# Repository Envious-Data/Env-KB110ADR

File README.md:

# Env-KB110ADR
A STM32F411CEU6 powered Mechanical keyboard PCB designed in KiCad

- Project Name: Env-KB110ADR
- Nickname: Victus

### About
I originally helped a friend design this but he couldnt quite figure out kicad nor had the motivation, It started out as a RP2040 powered 110% layout and then got cut down to a normal 100% and switched to a STM32F411CEU6.

It also support hotswap and ansi+iso.

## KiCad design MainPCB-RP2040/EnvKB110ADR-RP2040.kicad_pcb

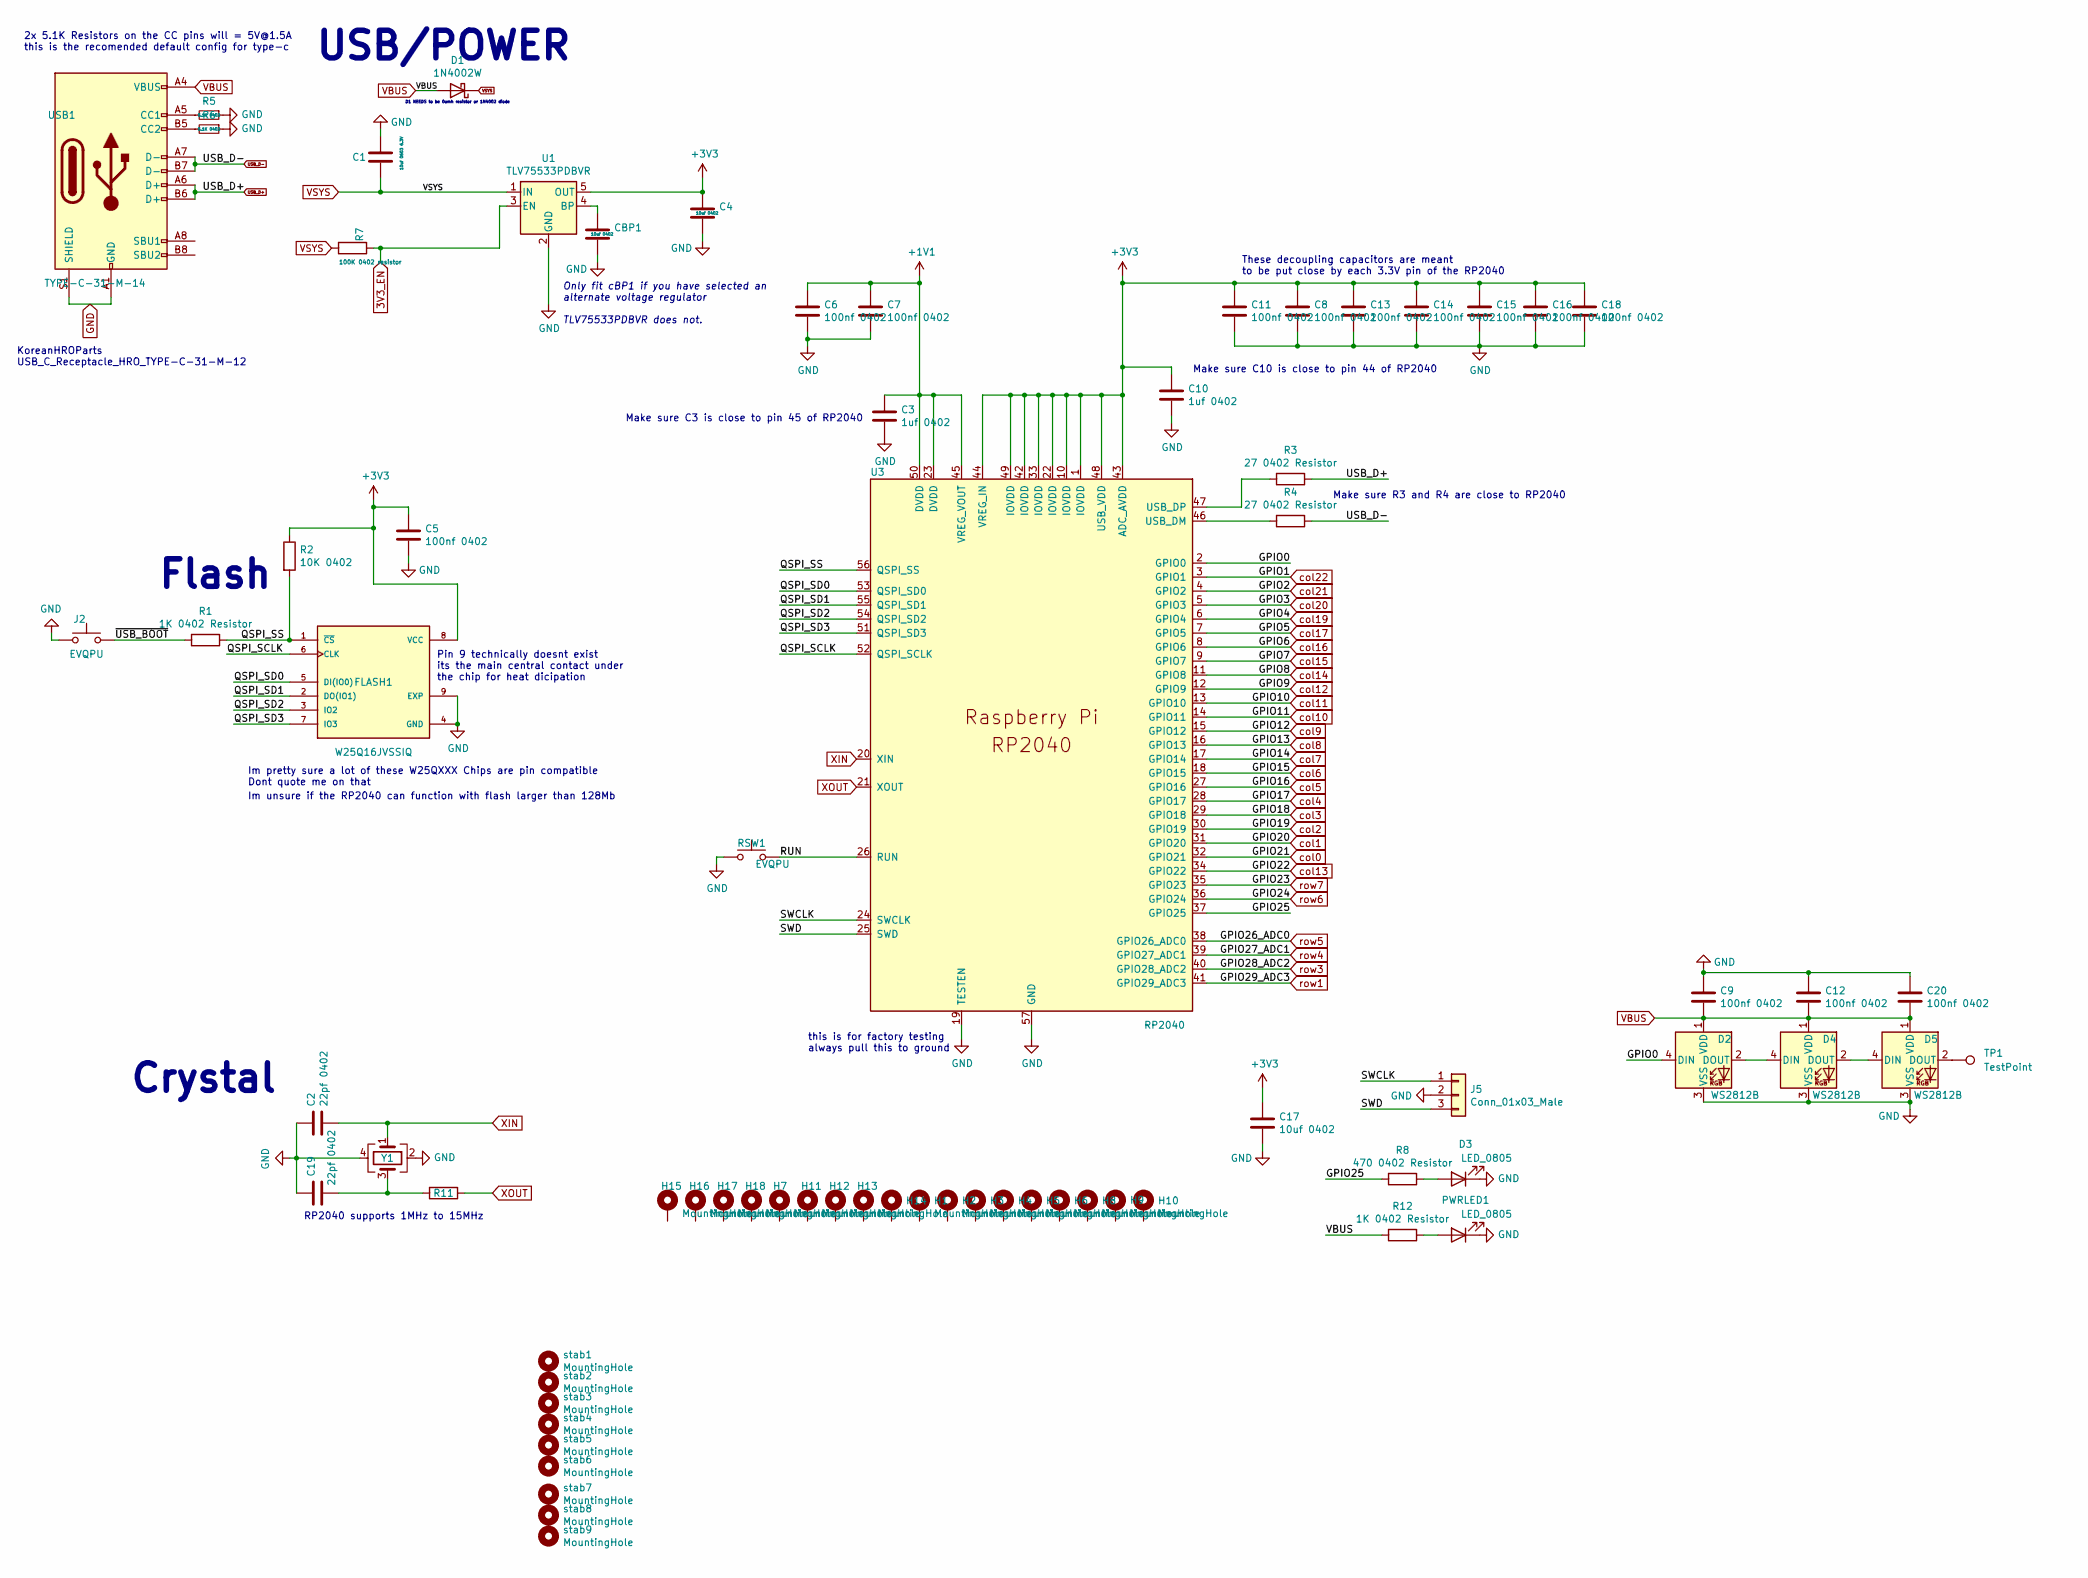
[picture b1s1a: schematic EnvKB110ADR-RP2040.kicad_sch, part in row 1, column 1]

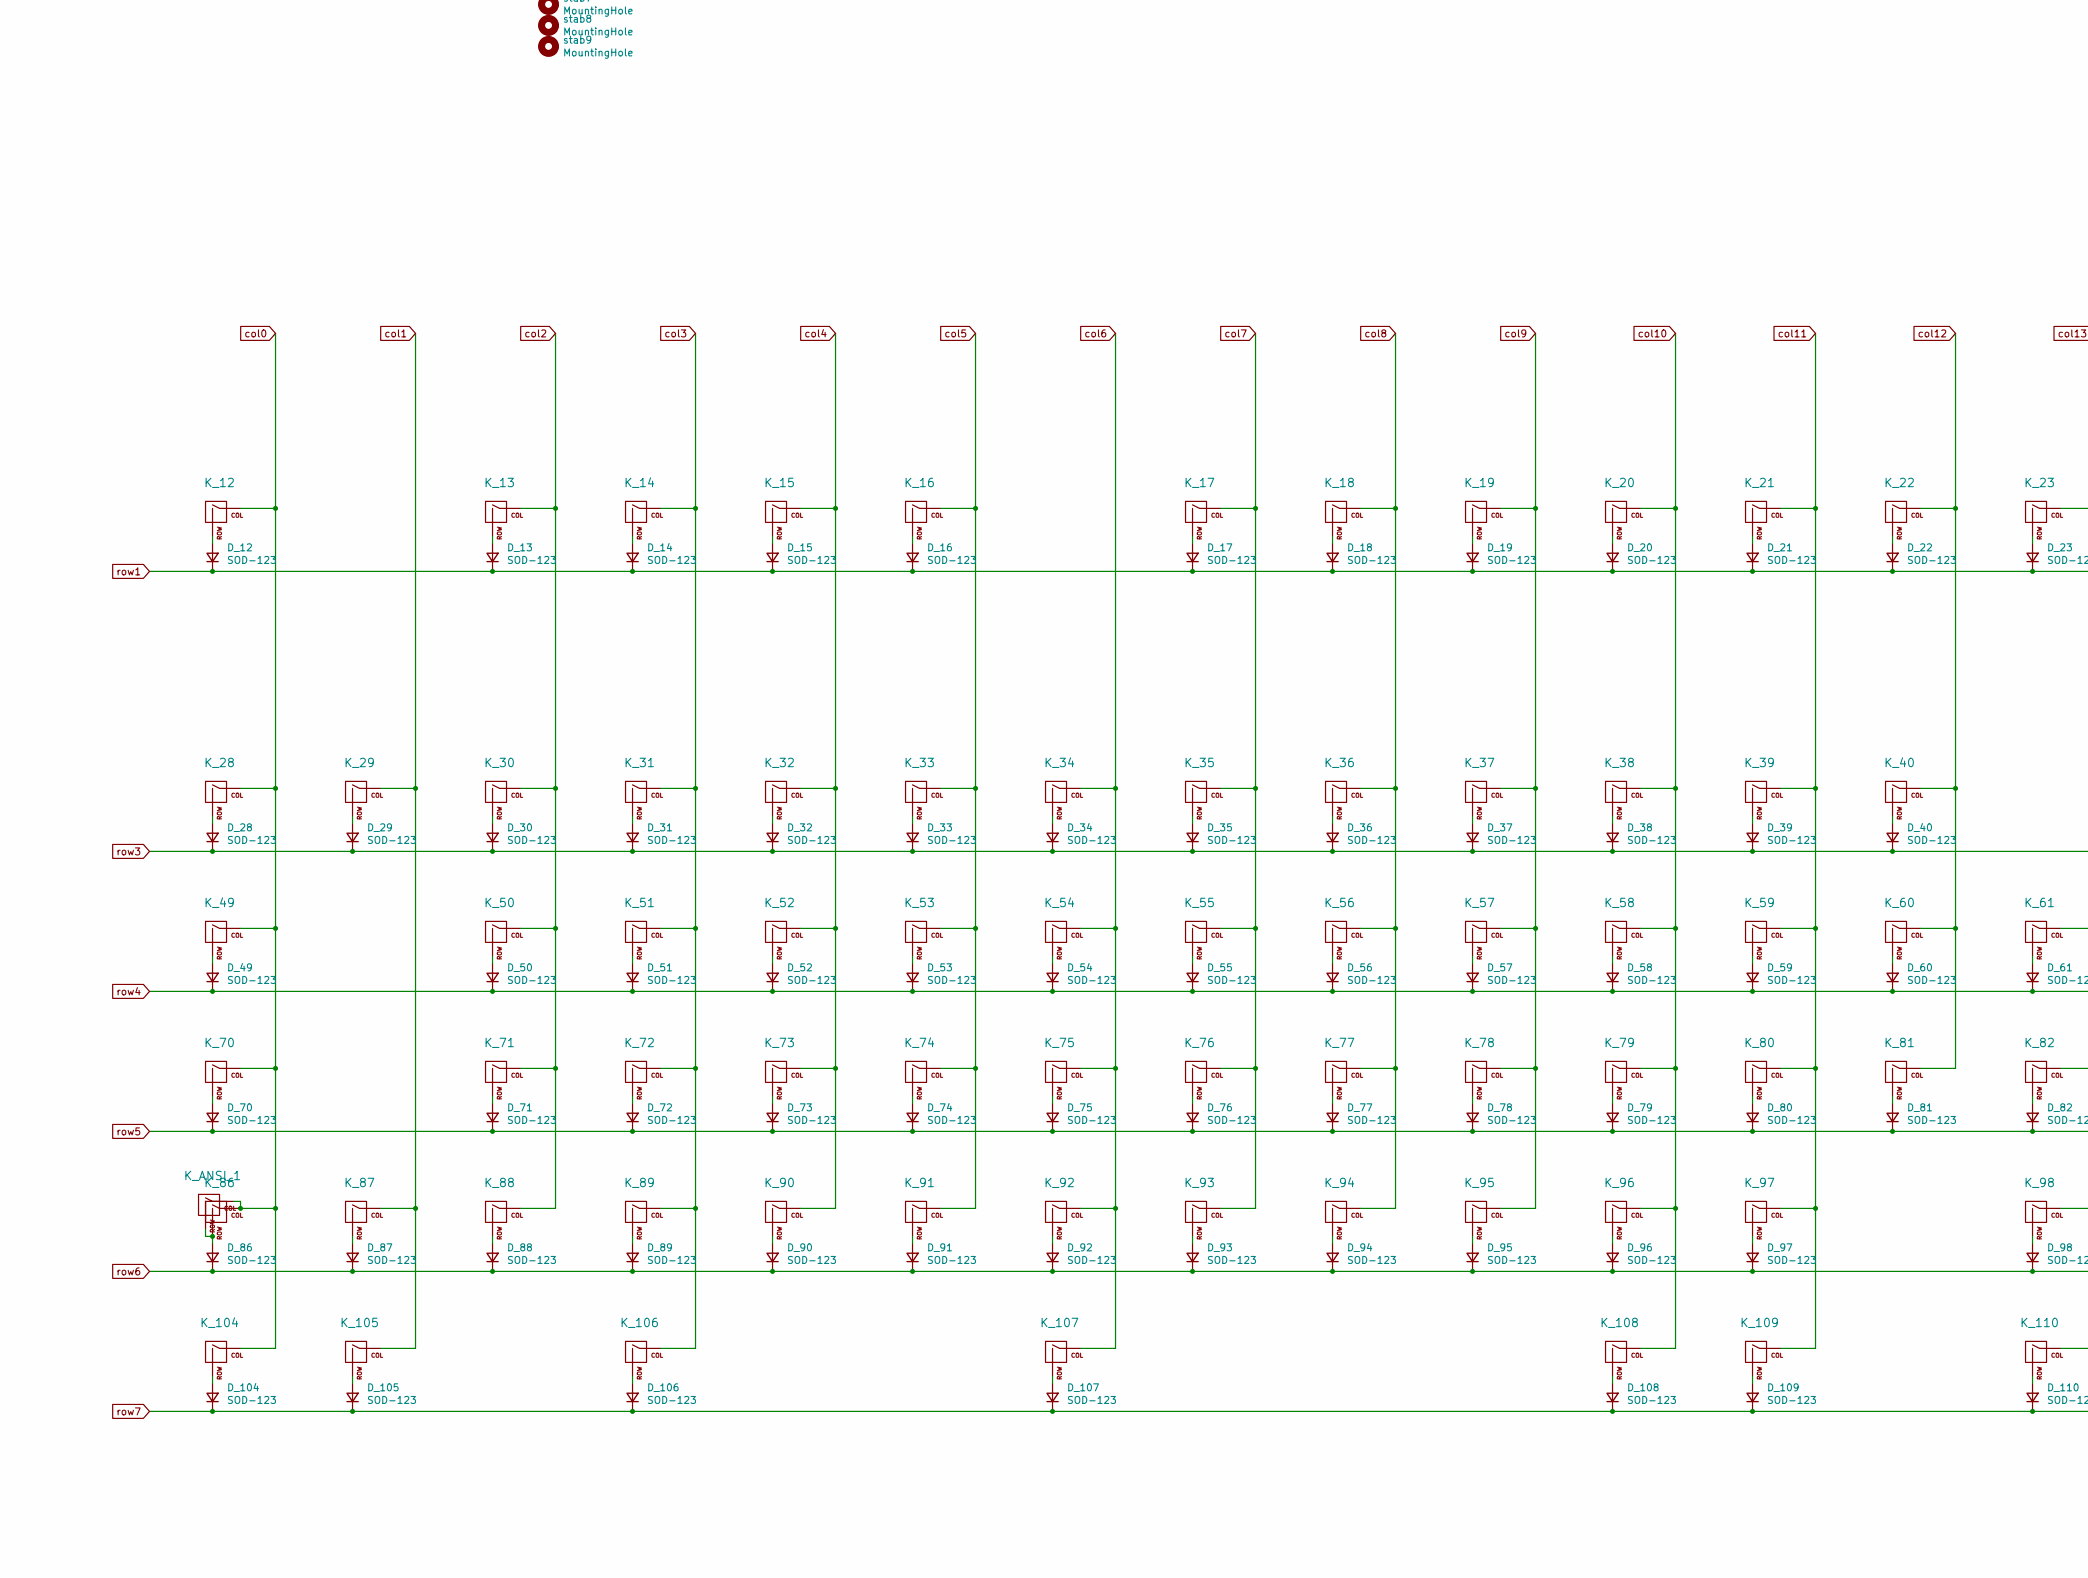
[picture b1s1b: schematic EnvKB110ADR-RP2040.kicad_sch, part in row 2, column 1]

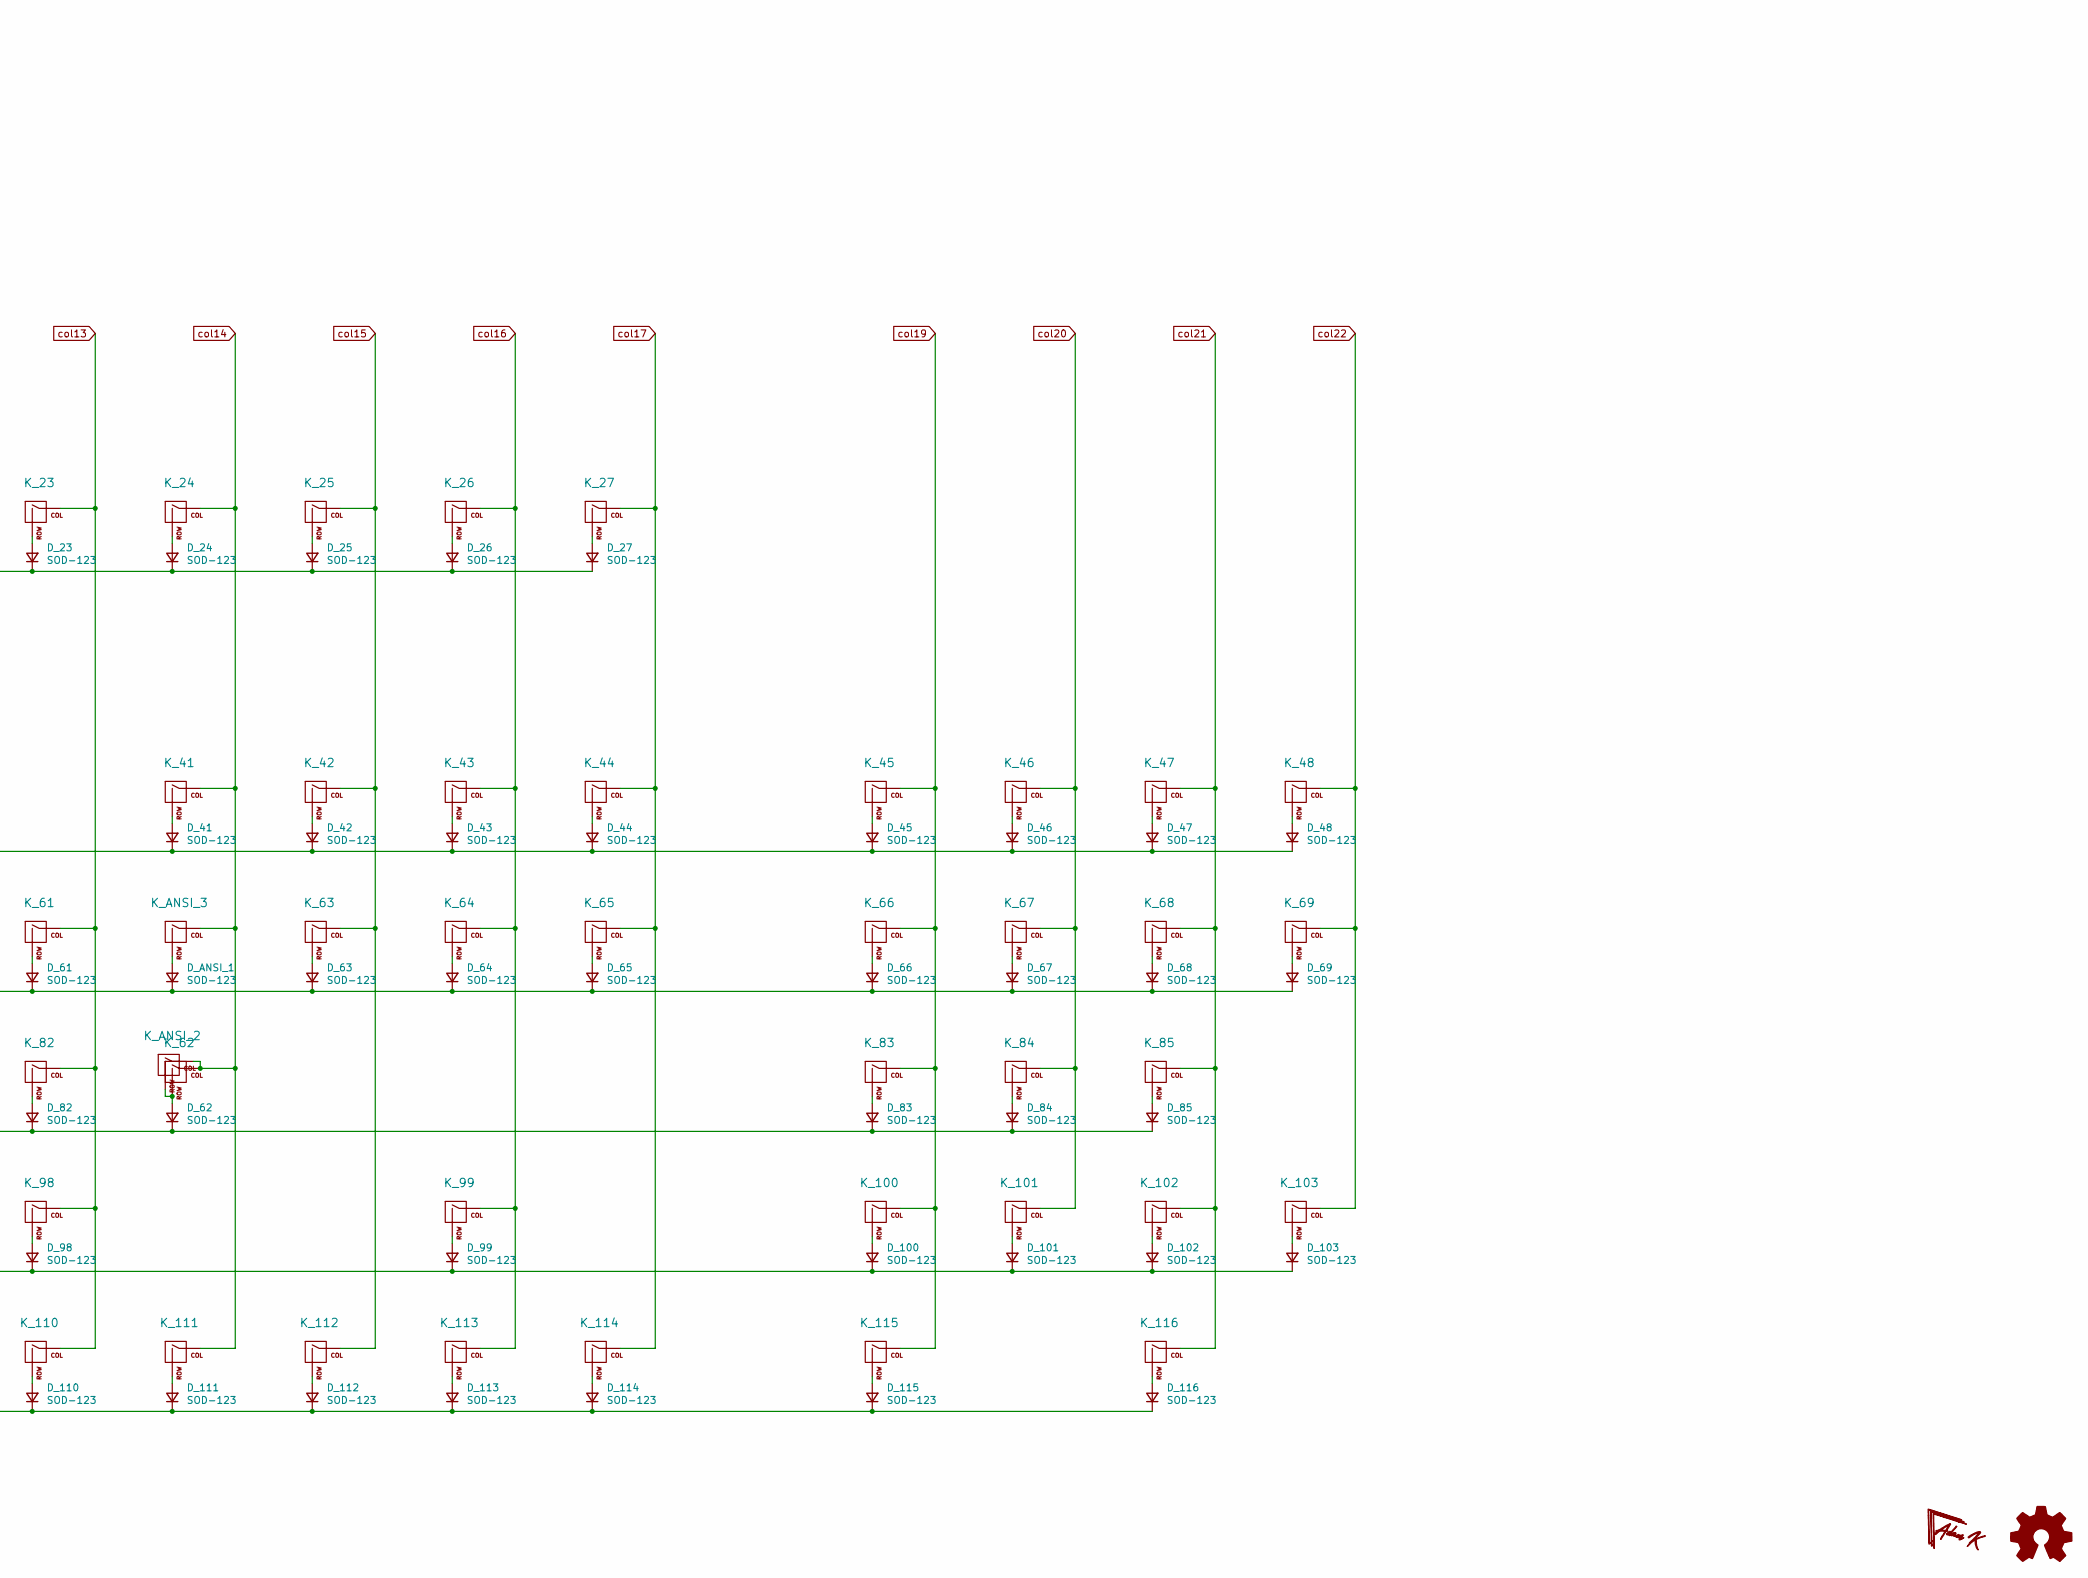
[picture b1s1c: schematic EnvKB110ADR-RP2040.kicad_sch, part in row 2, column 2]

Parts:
C1: 10uf 0603 6.3V; C_0603_1608Metric
C2, C19: 22pf 0402; C_0402_1005Metric
C3, C10: 1uf 0402; C_0402_1005Metric
C4, C17: 10uf 0402; C_0402_1005Metric
C5, C6, C7, C8, C9, C11, C12, C13, C14, C15, C16, C18, C20: 100nf 0402; C_0402_1005Metric
CBP1: 10uf 0402; C_0402_1005Metric
D1: 1N4002W; D_SOD-123
D2, D4, D5: WS2812B; LED_WS2812B_PLCC4_5.0x5.0mm_P3.2mm
D3: LED_0805; LED_0805_2012Metric
D_12, D_13, D_14, D_15, D_16, D_17, D_18, D_19, D_20, D_21, D_22, D_23, D_24, D_25, D_26, D_27, D_28, D_29, D_30, D_31, D_32, D_33, D_34, D_35, D_36, D_37, D_38, D_39, D_40, D_41, D_42, D_43, D_44, D_45, D_46, D_47, D_48, D_49, D_50, D_51, D_52, D_53, D_54, D_55, D_56, D_57, D_58, D_59, D_60, D_61, D_62, D_63, D_64, D_65, D_66, D_67, D_68, D_69, D_70, D_71, D_72, D_73, D_74, D_75, D_76, D_77, D_78, D_79, D_80, D_81, D_82, D_83, D_84, D_85, D_86, D_87, D_88, D_89, D_90, D_91, D_92, D_93, D_94, D_95, D_96, D_97, D_98, D_99, D_100, D_101, D_102, D_103, D_104, D_105, D_106, D_107, D_108, D_109, D_110, D_111, D_112, D_113, D_114, D_115, D_116: SOD-123; D_SOD-123
D_ANSI_1: SOD-123; D_SOD-123
FLASH1: W25Q16JVSSIQ; SOIC-8W_5.3x5.3mm_P1.27mm
H1, H2, H3, H4, H5, H6, H7, H8, H9, H10, H11, H12, H13, H14, H15, H16, H17, H18: MountingHole; MountingHole_2.2mm_M2_Pad
J2: EVQPU; Panasonic_EVQPUJ_EVQPUA
J5: Conn_01x03_Male; PinHeader_1x03_P2.54mm_Horizontal
K_12, K_13, K_14, K_15, K_16, K_17, K_18, K_19, K_20, K_21, K_22, K_23, K_24, K_25, K_26, K_27, K_28, K_29, K_30, K_31, K_32, K_33, K_34, K_35, K_36, K_37, K_38, K_39, K_40, K_41, K_42, K_43, K_44, K_45, K_46, K_47, K_48, K_49, K_50, K_51, K_52, K_53, K_54, K_55, K_56, K_57, K_58, K_59, K_60, K_61, K_62, K_63, K_64, K_65, K_66, K_67, K_68, K_69, K_70, K_71, K_72, K_73, K_74, K_75, K_76, K_77, K_78, K_79, K_80, K_81, K_82, K_83, K_84, K_85, K_86, K_87, K_88, K_89, K_90, K_91, K_92, K_93, K_94, K_95, K_96, K_97, K_98, K_99, K_100, K_101, K_102, K_103, K_104, K_105, K_106, K_107, K_108, K_109, K_110, K_111, K_112, K_113, K_114, K_115, K_116: KEYSW; MXOnly-1U-Hotswap-Modified
K_ANSI_1, K_ANSI_2, K_ANSI_3: KEYSW; MXOnly-1U-Hotswap-Modified
PWRLED1: LED_0805; LED_0805_2012Metric
R1, R11: 1K 0402 Resistor; C_0402_1005Metric
R2: 10K 0402; C_0402_1005Metric
R3, R4: 27 0402 Resistor; R_0402_1005Metric
R5, R6: 5.1K 0402; R_0402_1005Metric
R7: 100K 0402 resistor; R_0402_1005Metric
R8: 470 0402 Resistor; R_0402_1005Metric
R12: 1K 0402 Resistor; R_0402_1005Metric
RSW1: EVQPU; Panasonic_EVQPUJ_EVQPUA
TP1: TestPoint; TestPoint_Pad_4.0x4.0mm
U1: TLV75533PDBVR; SOT-23-5
U3: RP2040; RP2040-QFN-56; LCSC C2040
USB1: TYPE-C-31-M-14; USB_C_TYPE-C-31-M-14; MPN U262-161N-4BVC11; LCSC C319148
Y1: 3225_4P; Crystal_SMD_3225-4Pin_3.2x2.5mm
stab1, stab2, stab3, stab4, stab6, stab7, stab8, stab9: MountingHole; Stabilizer_Cherry_MX_2u
stab5: MountingHole; Stabilizer_Cherry_MX_6.25u

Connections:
3V3_EN: R7.1, U1.3 (EN)
+1V1: C3.1, C6.1, C7.1, U3.23 (DVDD), U3.45 (VREG_VOUT), U3.50 (DVDD)
+3V3: C4.1, C5.1, C8.1, C10.1, C11.1, C13.1, C14.1, C15.1, C16.1, C17.1, C18.1, FLASH1.8 (VCC), R2.1, U1.5 (OUT), U3.1 (IOVDD), U3.10 (IOVDD), U3.22 (IOVDD), U3.33 (IOVDD), U3.42 (IOVDD), U3.43 (ADC_AVDD), U3.44 (VREG_IN), U3.48 (USB_VDD), U3.49 (IOVDD)
/GPIO0: D2.4 (DIN), U3.2 (GPIO0)
/GPIO25: R8.2, U3.37 (GPIO25)
/QSPI_SCLK: FLASH1.6 (CLK), U3.52 (QSPI_SCLK)
/QSPI_SD0: FLASH1.5 (DI(IO0)), U3.53 (QSPI_SD0)
/QSPI_SD1: FLASH1.2 (DO(IO1)), U3.55 (QSPI_SD1)
/QSPI_SD2: FLASH1.3 (IO2), U3.54 (QSPI_SD2)
/QSPI_SD3: FLASH1.7 (IO3), U3.51 (QSPI_SD3)
/QSPI_SS: FLASH1.1 (~CS), R1.1, R2.2, U3.56 (QSPI_SS)
/RUN: RSW1.2, U3.26 (RUN)
/SWCLK: J5.1, U3.24 (SWCLK)
/SWD: J5.3, U3.25 (SWD)
/~USB_BOOT: J2.1, R1.2
GND: C1.2, C2.1, C3.2, C4.2, C5.2, C6.2, C7.2, C8.2, C9.1, C10.2, C11.2, C12.1, C13.2, C14.2, C15.2, C16.2, C17.2, C18.2, C19.1, C20.1, CBP1.2, D2.3 (VSS), D3.1 (K), D4.3 (VSS), D5.3 (VSS), FLASH1.4 (GND), FLASH1.9 (EXP), J2.2, J5.2, PWRLED1.1 (K), R5.1, R6.1, RSW1.1, U1.2 (GND), U3.19 (TESTEN), U3.57 (GND), USB1.A1 (GND), USB1.A12 (GND), USB1.B1 (GND), USB1.B12 (GND), USB1.S1 (SHIELD), Y1.2, Y1.4
unnamed: C19.2, R11.2, Y1.3
unnamed: CBP1.1, U1.4 (BP)
unnamed: D2.2 (DOUT), D4.4 (DIN)
unnamed: D3.2 (A), R8.1
unnamed: D4.2 (DOUT), D5.4 (DIN)
unnamed: D5.2 (DOUT), TP1.1
unnamed: D_12.2 (A), K_12.2 (ROW)
unnamed: D_13.2 (A), K_13.2 (ROW)
unnamed: D_14.2 (A), K_14.2 (ROW)
unnamed: D_15.2 (A), K_15.2 (ROW)
unnamed: D_16.2 (A), K_16.2 (ROW)
unnamed: D_17.2 (A), K_17.2 (ROW)
unnamed: D_18.2 (A), K_18.2 (ROW)
unnamed: D_19.2 (A), K_19.2 (ROW)
unnamed: D_20.2 (A), K_20.2 (ROW)
unnamed: D_21.2 (A), K_21.2 (ROW)
unnamed: D_22.2 (A), K_22.2 (ROW)
unnamed: D_23.2 (A), K_23.2 (ROW)
unnamed: D_24.2 (A), K_24.2 (ROW)
unnamed: D_25.2 (A), K_25.2 (ROW)
unnamed: D_26.2 (A), K_26.2 (ROW)
unnamed: D_27.2 (A), K_27.2 (ROW)
unnamed: D_28.2 (A), K_28.2 (ROW)
unnamed: D_29.2 (A), K_29.2 (ROW)
unnamed: D_30.2 (A), K_30.2 (ROW)
unnamed: D_31.2 (A), K_31.2 (ROW)
unnamed: D_32.2 (A), K_32.2 (ROW)
unnamed: D_33.2 (A), K_33.2 (ROW)
unnamed: D_34.2 (A), K_34.2 (ROW)
unnamed: D_35.2 (A), K_35.2 (ROW)
unnamed: D_36.2 (A), K_36.2 (ROW)
unnamed: D_37.2 (A), K_37.2 (ROW)
unnamed: D_38.2 (A), K_38.2 (ROW)
unnamed: D_39.2 (A), K_39.2 (ROW)
unnamed: D_40.2 (A), K_40.2 (ROW)
unnamed: D_41.2 (A), K_41.2 (ROW)
unnamed: D_42.2 (A), K_42.2 (ROW)
unnamed: D_43.2 (A), K_43.2 (ROW)
unnamed: D_44.2 (A), K_44.2 (ROW)
unnamed: D_45.2 (A), K_45.2 (ROW)
unnamed: D_46.2 (A), K_46.2 (ROW)
unnamed: D_47.2 (A), K_47.2 (ROW)
unnamed: D_48.2 (A), K_48.2 (ROW)
unnamed: D_49.2 (A), K_49.2 (ROW)
unnamed: D_50.2 (A), K_50.2 (ROW)
unnamed: D_51.2 (A), K_51.2 (ROW)
unnamed: D_52.2 (A), K_52.2 (ROW)
unnamed: D_53.2 (A), K_53.2 (ROW)
unnamed: D_54.2 (A), K_54.2 (ROW)
unnamed: D_55.2 (A), K_55.2 (ROW)
unnamed: D_56.2 (A), K_56.2 (ROW)
unnamed: D_57.2 (A), K_57.2 (ROW)
unnamed: D_58.2 (A), K_58.2 (ROW)
unnamed: D_59.2 (A), K_59.2 (ROW)
unnamed: D_60.2 (A), K_60.2 (ROW)
unnamed: D_61.2 (A), K_61.2 (ROW)
unnamed: D_62.2 (A), K_62.2 (ROW), K_ANSI_2.2 (ROW)
unnamed: D_63.2 (A), K_63.2 (ROW)
unnamed: D_64.2 (A), K_64.2 (ROW)
unnamed: D_65.2 (A), K_65.2 (ROW)
unnamed: D_66.2 (A), K_66.2 (ROW)
unnamed: D_67.2 (A), K_67.2 (ROW)
unnamed: D_68.2 (A), K_68.2 (ROW)
unnamed: D_69.2 (A), K_69.2 (ROW)
unnamed: D_70.2 (A), K_70.2 (ROW)
unnamed: D_71.2 (A), K_71.2 (ROW)
unnamed: D_72.2 (A), K_72.2 (ROW)
unnamed: D_73.2 (A), K_73.2 (ROW)
unnamed: D_74.2 (A), K_74.2 (ROW)
unnamed: D_75.2 (A), K_75.2 (ROW)
unnamed: D_76.2 (A), K_76.2 (ROW)
unnamed: D_77.2 (A), K_77.2 (ROW)
unnamed: D_78.2 (A), K_78.2 (ROW)
unnamed: D_79.2 (A), K_79.2 (ROW)
unnamed: D_80.2 (A), K_80.2 (ROW)
unnamed: D_81.2 (A), K_81.2 (ROW)
unnamed: D_82.2 (A), K_82.2 (ROW)
unnamed: D_83.2 (A), K_83.2 (ROW)
unnamed: D_84.2 (A), K_84.2 (ROW)
unnamed: D_85.2 (A), K_85.2 (ROW)
unnamed: D_86.2 (A), K_86.2 (ROW), K_ANSI_1.2 (ROW)
unnamed: D_87.2 (A), K_87.2 (ROW)
unnamed: D_88.2 (A), K_88.2 (ROW)
unnamed: D_89.2 (A), K_89.2 (ROW)
unnamed: D_90.2 (A), K_90.2 (ROW)
unnamed: D_91.2 (A), K_91.2 (ROW)
unnamed: D_92.2 (A), K_92.2 (ROW)
unnamed: D_93.2 (A), K_93.2 (ROW)
unnamed: D_94.2 (A), K_94.2 (ROW)
unnamed: D_95.2 (A), K_95.2 (ROW)
unnamed: D_96.2 (A), K_96.2 (ROW)
unnamed: D_97.2 (A), K_97.2 (ROW)
unnamed: D_98.2 (A), K_98.2 (ROW)
unnamed: D_99.2 (A), K_99.2 (ROW)
unnamed: D_100.2 (A), K_100.2 (ROW)
unnamed: D_101.2 (A), K_101.2 (ROW)
unnamed: D_102.2 (A), K_102.2 (ROW)
unnamed: D_103.2 (A), K_103.2 (ROW)
unnamed: D_104.2 (A), K_104.2 (ROW)
unnamed: D_105.2 (A), K_105.2 (ROW)
unnamed: D_106.2 (A), K_106.2 (ROW)
unnamed: D_107.2 (A), K_107.2 (ROW)
unnamed: D_108.2 (A), K_108.2 (ROW)
unnamed: D_109.2 (A), K_109.2 (ROW)
unnamed: D_110.2 (A), K_110.2 (ROW)
unnamed: D_111.2 (A), K_111.2 (ROW)
unnamed: D_112.2 (A), K_112.2 (ROW)
unnamed: D_113.2 (A), K_113.2 (ROW)
unnamed: D_114.2 (A), K_114.2 (ROW)
unnamed: D_115.2 (A), K_115.2 (ROW)
unnamed: D_116.2 (A), K_116.2 (ROW)
unnamed: D_ANSI_1.2 (A), K_ANSI_3.2 (ROW)
unnamed: PWRLED1.2 (A), R12.1
unnamed: R3.2, U3.47 (USB_DP)
unnamed: R4.2, U3.46 (USB_DM)
unnamed: R5.2, USB1.A5 (CC1)
unnamed: R6.2, USB1.B5 (CC2)
USB_D+: R3.1, USB1.A6 (D+), USB1.B6 (D+)
USB_D-: R4.1, USB1.A7 (D-), USB1.B7 (D-)
VBUS: C9.2, C12.2, C20.2, D1.2 (A), D2.1 (VDD), D4.1 (VDD), D5.1 (VDD), R12.2, USB1.A4 (VBUS), USB1.A9 (VBUS), USB1.B4 (VBUS), USB1.B9 (VBUS)
VSYS: C1.1, D1.1 (K), R7.2, U1.1 (IN)
XIN: C2.2, U3.20 (XIN), Y1.1
XOUT: R11.1, U3.21 (XOUT)
col0: K_12.1 (COL), K_28.1 (COL), K_49.1 (COL), K_70.1 (COL), K_86.1 (COL), K_104.1 (COL), K_ANSI_1.1 (COL), U3.32 (GPIO21)
col1: K_29.1 (COL), K_87.1 (COL), K_105.1 (COL), U3.31 (GPIO20)
col2: K_13.1 (COL), K_30.1 (COL), K_50.1 (COL), K_71.1 (COL), K_88.1 (COL), U3.30 (GPIO19)
col3: K_14.1 (COL), K_31.1 (COL), K_51.1 (COL), K_72.1 (COL), K_89.1 (COL), K_106.1 (COL), U3.29 (GPIO18)
col4: K_15.1 (COL), K_32.1 (COL), K_52.1 (COL), K_73.1 (COL), K_90.1 (COL), U3.28 (GPIO17)
col5: K_16.1 (COL), K_33.1 (COL), K_53.1 (COL), K_74.1 (COL), K_91.1 (COL), U3.27 (GPIO16)
col6: K_34.1 (COL), K_54.1 (COL), K_75.1 (COL), K_92.1 (COL), K_107.1 (COL), U3.18 (GPIO15)
col7: K_17.1 (COL), K_35.1 (COL), K_55.1 (COL), K_76.1 (COL), K_93.1 (COL), U3.17 (GPIO14)
col8: K_18.1 (COL), K_36.1 (COL), K_56.1 (COL), K_77.1 (COL), K_94.1 (COL), U3.16 (GPIO13)
col9: K_19.1 (COL), K_37.1 (COL), K_57.1 (COL), K_78.1 (COL), K_95.1 (COL), U3.15 (GPIO12)
col10: K_20.1 (COL), K_38.1 (COL), K_58.1 (COL), K_79.1 (COL), K_96.1 (COL), K_108.1 (COL), U3.14 (GPIO11)
col11: K_21.1 (COL), K_39.1 (COL), K_59.1 (COL), K_80.1 (COL), K_97.1 (COL), K_109.1 (COL), U3.13 (GPIO10)
col12: K_22.1 (COL), K_40.1 (COL), K_60.1 (COL), K_81.1 (COL), U3.12 (GPIO9)
col13: K_23.1 (COL), K_61.1 (COL), K_82.1 (COL), K_98.1 (COL), K_110.1 (COL), U3.34 (GPIO22)
col14: K_24.1 (COL), K_41.1 (COL), K_62.1 (COL), K_111.1 (COL), K_ANSI_2.1 (COL), K_ANSI_3.1 (COL), U3.11 (GPIO8)
col15: K_25.1 (COL), K_42.1 (COL), K_63.1 (COL), K_112.1 (COL), U3.9 (GPIO7)
col16: K_26.1 (COL), K_43.1 (COL), K_64.1 (COL), K_99.1 (COL), K_113.1 (COL), U3.8 (GPIO6)
col17: K_27.1 (COL), K_44.1 (COL), K_65.1 (COL), K_114.1 (COL), U3.7 (GPIO5)
col19: K_45.1 (COL), K_66.1 (COL), K_83.1 (COL), K_100.1 (COL), K_115.1 (COL), U3.6 (GPIO4)
col20: K_46.1 (COL), K_67.1 (COL), K_84.1 (COL), K_101.1 (COL), U3.5 (GPIO3)
col21: K_47.1 (COL), K_68.1 (COL), K_85.1 (COL), K_102.1 (COL), K_116.1 (COL), U3.4 (GPIO2)
col22: K_48.1 (COL), K_69.1 (COL), K_103.1 (COL), U3.3 (GPIO1)
row1: D_12.1 (K), D_13.1 (K), D_14.1 (K), D_15.1 (K), D_16.1 (K), D_17.1 (K), D_18.1 (K), D_19.1 (K), D_20.1 (K), D_21.1 (K), D_22.1 (K), D_23.1 (K), D_24.1 (K), D_25.1 (K), D_26.1 (K), D_27.1 (K), U3.41 (GPIO29_ADC3)
row3: D_28.1 (K), D_29.1 (K), D_30.1 (K), D_31.1 (K), D_32.1 (K), D_33.1 (K), D_34.1 (K), D_35.1 (K), D_36.1 (K), D_37.1 (K), D_38.1 (K), D_39.1 (K), D_40.1 (K), D_41.1 (K), D_42.1 (K), D_43.1 (K), D_44.1 (K), D_45.1 (K), D_46.1 (K), D_47.1 (K), D_48.1 (K), U3.40 (GPIO28_ADC2)
row4: D_49.1 (K), D_50.1 (K), D_51.1 (K), D_52.1 (K), D_53.1 (K), D_54.1 (K), D_55.1 (K), D_56.1 (K), D_57.1 (K), D_58.1 (K), D_59.1 (K), D_60.1 (K), D_61.1 (K), D_63.1 (K), D_64.1 (K), D_65.1 (K), D_66.1 (K), D_67.1 (K), D_68.1 (K), D_69.1 (K), D_ANSI_1.1 (K), U3.39 (GPIO27_ADC1)
row5: D_62.1 (K), D_70.1 (K), D_71.1 (K), D_72.1 (K), D_73.1 (K), D_74.1 (K), D_75.1 (K), D_76.1 (K), D_77.1 (K), D_78.1 (K), D_79.1 (K), D_80.1 (K), D_81.1 (K), D_82.1 (K), D_83.1 (K), D_84.1 (K), D_85.1 (K), U3.38 (GPIO26_ADC0)
row6: D_86.1 (K), D_87.1 (K), D_88.1 (K), D_89.1 (K), D_90.1 (K), D_91.1 (K), D_92.1 (K), D_93.1 (K), D_94.1 (K), D_95.1 (K), D_96.1 (K), D_97.1 (K), D_98.1 (K), D_99.1 (K), D_100.1 (K), D_101.1 (K), D_102.1 (K), D_103.1 (K), U3.36 (GPIO24)
row7: D_104.1 (K), D_105.1 (K), D_106.1 (K), D_107.1 (K), D_108.1 (K), D_109.1 (K), D_110.1 (K), D_111.1 (K), D_112.1 (K), D_113.1 (K), D_114.1 (K), D_115.1 (K), D_116.1 (K), U3.35 (GPIO23)

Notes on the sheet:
Only fit cBP1 if you have selected an alternate voltage regulator TLV75533PDBVR does not.
Im pretty sure a lot of these W25QXXX Chips are pin compatible Dont quote me on that
KoreanHROParts USB_C_Receptacle_HRO_TYPE-C-31-M-12
Crystal
2x 5.1K Resistors on the CC pins will = 5V@1.5A this is the recomended default config for type-c
this is for factory testing always pull this to ground
Make sure R3 and R4 are close to RP2040
These decoupling capacitors are meant to be put close by each 3.3V pin of the RP2040
D1 NEEDS to be 0omh resistor or 1N4002 diode
USB/POWER
Flash
Im unsure if the RP2040 can function with flash larger than 128Mb
Make sure C10 is close to pin 44 of RP2040
RP2040 supports 1MHz to 15MHz
Make sure C3 is close to pin 45 of RP2040
Pin 9 technically doesnt exist its the main central contact under the chip for heat dicipation

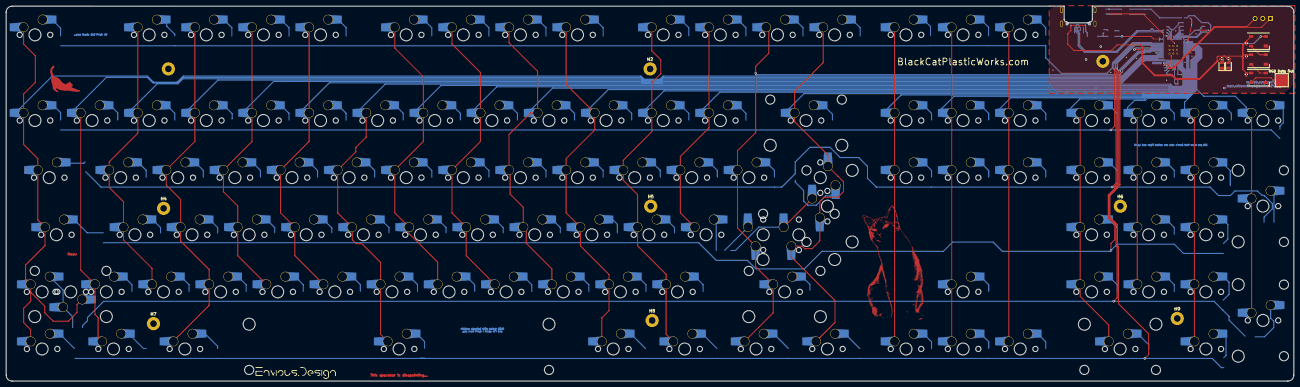
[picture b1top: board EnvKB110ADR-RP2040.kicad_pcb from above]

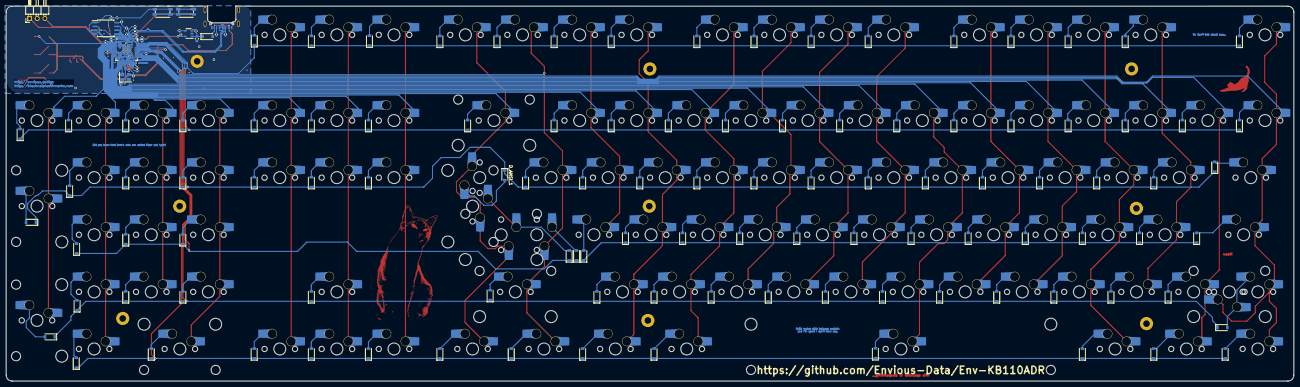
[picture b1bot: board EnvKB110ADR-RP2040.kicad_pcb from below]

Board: 2 copper layers, 429.5 x 125.0 mm, 279 parts (141 on the bottom side), 167 nets.

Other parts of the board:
kibuzzard-6261CED5: G***; kibuzzard-6261CED5

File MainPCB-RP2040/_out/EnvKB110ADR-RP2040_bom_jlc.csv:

"Comment","Designator","Footprint","LCSC Part #"
"10uf 0603 6.3V","C1","C_0603_1608Metric","no_part_number"
"22pf 0402","C2,C19","C_0402_1005Metric","no_part_number"
"1uf 0402","C3,C10","C_0402_1005Metric","no_part_number"
"10uf 0402","C4,C17","C_0402_1005Metric","no_part_number"
"100nf 0402","C5,C6,C7,C8,C9,C11,C12,C13,C14,C15,C16,C18,C20","C_0402_1005Metric","no_part_number"
"10uf 0402","CBP1","C_0402_1005Metric","no_part_number"
"1N4002W","D1","D_SOD-123","no_part_number"
"WS2812B","D2,D4,D5","LED_WS2812B_PLCC4_5.0x5.0mm_P3.2mm","no_part_number"
"LED_0805","D3","LED_0805_2012Metric","no_part_number"
"SOD-123","D_12,D_13,D_14,D_15,D_16,D_17,D_18,D_19,D_20,D_21,D_22,D_23,D_24,D_25,D_26,D_27,D_28,D_29,D_30,D_31,D_32,D_33,D_34,D_35,D_36,D_37,D_38,D_39,D_40,D_41,D_42,D_43,D_44,D_45,D_46,D_47,D_48,D_49,D_50,D_51,D_52,D_53,D_54,D_55,D_56,D_57,D_58,D_59,D_60,D_61,D_62,D_63,D_64,D_65,D_66,D_67,D_68,D_69,D_70,D_71,D_72,D_73,D_74,D_75,D_76,D_77,D_78,D_79,D_80,D_81,D_82,D_83,D_84,D_85,D_86,D_87,D_88,D_89,D_90,D_91,D_92,D_93,D_94,D_95,D_96,D_97,D_98,D_99,D_100,D_101,D_102,D_103,D_104,D_105,D_106,D_107,D_108,D_109,D_110,D_111,D_112,D_113,D_114,D_115,D_116","D_SOD-123","no_part_number"
"SOD-123","D_ANSI_1","D_SOD-123","no_part_number"
"W25Q16JVSSIQ","FLASH1","SOIC-8W_5.3x5.3mm_P1.27mm","no_part_number"
"MountingHole","H1,H2,H3,H4,H5,H6,H7,H8,H9,H10,H11,H12,H13,H14,H15,H16,H17,H18","MountingHole_2.2mm_M2_Pad","no_part_number"
"EVQPU","J2","Panasonic_EVQPUJ_EVQPUA","no_part_number"
"Conn_01x03_Male","J5","PinHeader_1x03_P2.54mm_Horizontal","no_part_number"
"KEYSW","K_12,K_13,K_14,K_15,K_16,K_17,K_18,K_19,K_20,K_21,K_22,K_23,K_24,K_25,K_26,K_27,K_28,K_29,K_30,K_31,K_32,K_33,K_34,K_35,K_36,K_37,K_38,K_39,K_40,K_41,K_42,K_43,K_44,K_45,K_46,K_47,K_48,K_49,K_50,K_51,K_52,K_53,K_54,K_55,K_56,K_57,K_58,K_59,K_60,K_61,K_62,K_63,K_64,K_65,K_66,K_67,K_68,K_69,K_70,K_71,K_72,K_73,K_74,K_75,K_76,K_77,K_78,K_79,K_80,K_81,K_82,K_83,K_84,K_85,K_86,K_87,K_88,K_89,K_90,K_91,K_92,K_93,K_94,K_95,K_96,K_97,K_98,K_99,K_100,K_101,K_102,K_103,K_104,K_105,K_106,K_107,K_108,K_109,K_110,K_111,K_112,K_113,K_114,K_115,K_116","MXOnly-1U-Hotswap-Modified","no_part_number"
"KEYSW","K_ANSI_1,K_ANSI_2,K_ANSI_3","MXOnly-1U-Hotswap-Modified","no_part_number"
"LED_0805","PWRLED1","LED_0805_2012Metric","no_part_number"
"1K 0402 Resistor","R1,R11","C_0402_1005Metric","no_part_number"
"10K 0402","R2","C_0402_1005Metric","no_part_number"
"27 0402 Resistor","R3,R4","R_0402_1005Metric","no_part_number"
"5.1K 0402","R5,R6","R_0402_1005Metric","no_part_number"
"100K 0402 resistor","R7","R_0402_1005Metric","no_part_number"
"470 0402 Resistor","R8","R_0402_1005Metric","no_part_number"
"1K 0402 Resistor","R12","R_0402_1005Metric","no_part_number"
"EVQPU","RSW1","Panasonic_EVQPUJ_EVQPUA","no_part_number"
"MountingHole","stab1,stab2,stab3,stab4,stab6,stab7,stab8,stab9","Stabilizer_Cherry_MX_2u","no_part_number"
"MountingHole","stab5","Stabilizer_Cherry_MX_6.25u","no_part_number"
"TestPoint","TP1","TestPoint_Pad_4.0x4.0mm","no_part_number"
"TLV75533PDBVR","U1","SOT-23-5","no_part_number"
"RP2040","U3","RP2040-QFN-56","C2040"
"TYPE-C-31-M-14","USB1","USB_C_TYPE-C-31-M-14","C319148"
"3225_4P","Y1","Crystal_SMD_3225-4Pin_3.2x2.5mm","no_part_number"

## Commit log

2021-06-15 some corrections as per DRC - 2 unconnected items
2021-06-15 Trying to prettify traces (Abysmal job of it)
2021-06-16 Corrected some errors and fixed the enter key traces
2021-06-16 setup some board bits
2021-06-16 Removed some overlapping and pointless traces.
2021-06-17 Modified Kicad Projects to make generating DXFs for laser cutting easier.
2021-06-20 Made some tweaks to allow for easier Gerber generation
2021-07-04 Started work on swapping RPI pico for STM32F411CEU6
2021-07-04 added some notes in the schematic
2021-07-04 hopefully correct implementation of a 8mhz oscilator
2021-07-05 added boot and reset switches
2021-07-05 added decoupling capacitors for LDO
2021-07-05 annotated parts + notes adjustment
2021-07-05 Updated PCB to have new parts
2021-07-10 Added row/col pins in the schematic for pcbnew to show them
2021-09-21 See List
    - Added ANSI support
    - redone sections of the board to fit ansi support
    - edited all footprints to have through holes so they can be connected on both sides.
    - probably a bunch of other shite
2021-09-21 more progress, working on column traces.
2021-09-21 finished up traces and added a cat silkscreen.
2021-09-24 Corrected a trace going through a hole
2021-09-24 removed incorrect backplate and switch plate, I will re-make this in the future once the main PCB is a bit closer to being finished.
2021-09-24 Cleaned up folder layout a bit.
2021-09-24 deleted old BOM
2021-09-24 changed oscillator for crystal, re-added libraries, made change in PCBNew
2021-09-28 Small fixes and corrections
2021-09-28 some general changes, might change MCU to RP2040
2021-09-28 Converted board from STM32F411CEU6 to RP2040
2021-09-28 wired up all the traces required to make the keyboard functional.
    However this means you can no longer use the Rpi pico firmware with this and needs a custom compiled firmware to utilize the normally unavailable pins,
2021-09-28 Generated updated gerbers
2021-09-28 Replaced flash with smaller uson-8 3x2 + regenerated Gerbers
2021-09-28 corrected small issue and updated gerber again
2021-09-28 Decided to retain STM32F411CEU6 version and also made symlink for shared resources
2021-09-28 Flipped STM32 to other side of board and added a debug header (SWDIO/SWCLK)
2021-09-30 added mount holes, fixed a couple trace errors, created backplate PCB
2021-09-30 Created switch plate
2021-09-30 padded switch plate and generated gerber for test price (£19.43)
2021-09-30 forgot to commit this change lol.
2021-10-02 comitted some changes made
2021-10-22 small corrections and mild cleanup
2021-10-22 generated updated Gerber for RP2040 Version
2021-10-26 cleaned a couple derps up.
2021-10-28 corrections to design, via in pad and such
2021-11-19 added logo for black cat plastic works, couple urls and some fixes to design
2021-11-19 moved site name up a bit
2021-11-21 general corrections and tweaks
2021-11-25 replaced switch footprints with stronger versions and SMT assembly compatible versions
2021-11-30 general adjustments, fixes and tweaks on STM32 version
2021-11-30 Corrected inverted traces I think.
2021-11-30 added missing capacitor on vcap
2021-11-30 added missing capacitor and power connection
2021-12-05 Generated updated Gerber
2022-01-11 fixed a random trace that was left over from something else.
2022-01-15 updated PCB to fit stocked JLC Parts and added BOM and CPL to .gitignore
2022-01-15 added missing stabilizers and updated gerber
2022-01-16 some corrections and adjustments regarding 3.3v decoupling capacitors.
2022-01-16 updated gerbers
2022-01-16 swapped port for mid-mount version
2022-01-16 updated Gerber again
2022-01-18 updated gerber again and exported some layers and what not.
2022-01-27 Added part number for the nor flash and also changed footprint to correct one? also added some smol easter eggs.
2022-04-17 various improvements/ made ISO only (for now maybe)
2022-04-21 properly implemented ANSI/ISO support.
2022-04-21 various updates and adjustments
2022-04-22 Generated Gerber to check price
2022-06-07 made version with rpi pico and io expander
2022-06-07 moved some 3d models locally
2022-06-07 generated gerber, bom and cpl
2022-06-07 fixed ref and generated updated gerber
2022-06-07 changed switch plates to fit thicker materials
2022-06-07 sorted reference out
2022-06-11 swapped IO expander package to DIP
2022-06-11 Added position for OLED and RGB indicator LEDs among other things
2022-06-11 some adjustments to make CAD a bit easier
2022-06-11 Changed my mind on Mount holes
2022-06-24 added 7u bottom and stepped capslock
2022-07-02 various small adjustments
2022-12-01 some general tweaks and preparation for ordering
2023-05-25 removed variants in favor of RP2040 version with no IO expander, needs finishing up
2023-05-25 Various fixes to clearances and fixed a lot of traces
2023-05-25 Made solder version and fixed up all its issues
2023-05-25 small fix to gitignore
2023-05-25 adjusted mount holes
2023-05-25 updated some bits
2023-05-25 generated Gerbers for solder version
2023-05-25 generated files to be used to model case
2023-06-22 cleanup and swapped MCU to PGA2040 on solder version as experiment.
2023-06-22 swapped buttons to Panasonic side buttons and wired up debug header
2023-06-22 some small fixes and adjustments to mount holes
2023-06-22 Generated production files
2024-04-29 replaced PGA2040 with STM32F401
2024-04-29 tweaked a couple connections to avoid problems
2024-04-29 tweaked silkscreen mark
2024-05-02 some measurement tweaks
